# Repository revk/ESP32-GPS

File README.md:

# ESP32-GPS

Now at [Codeberg](https://codeberg.org/RevK/ESP32-GPS)

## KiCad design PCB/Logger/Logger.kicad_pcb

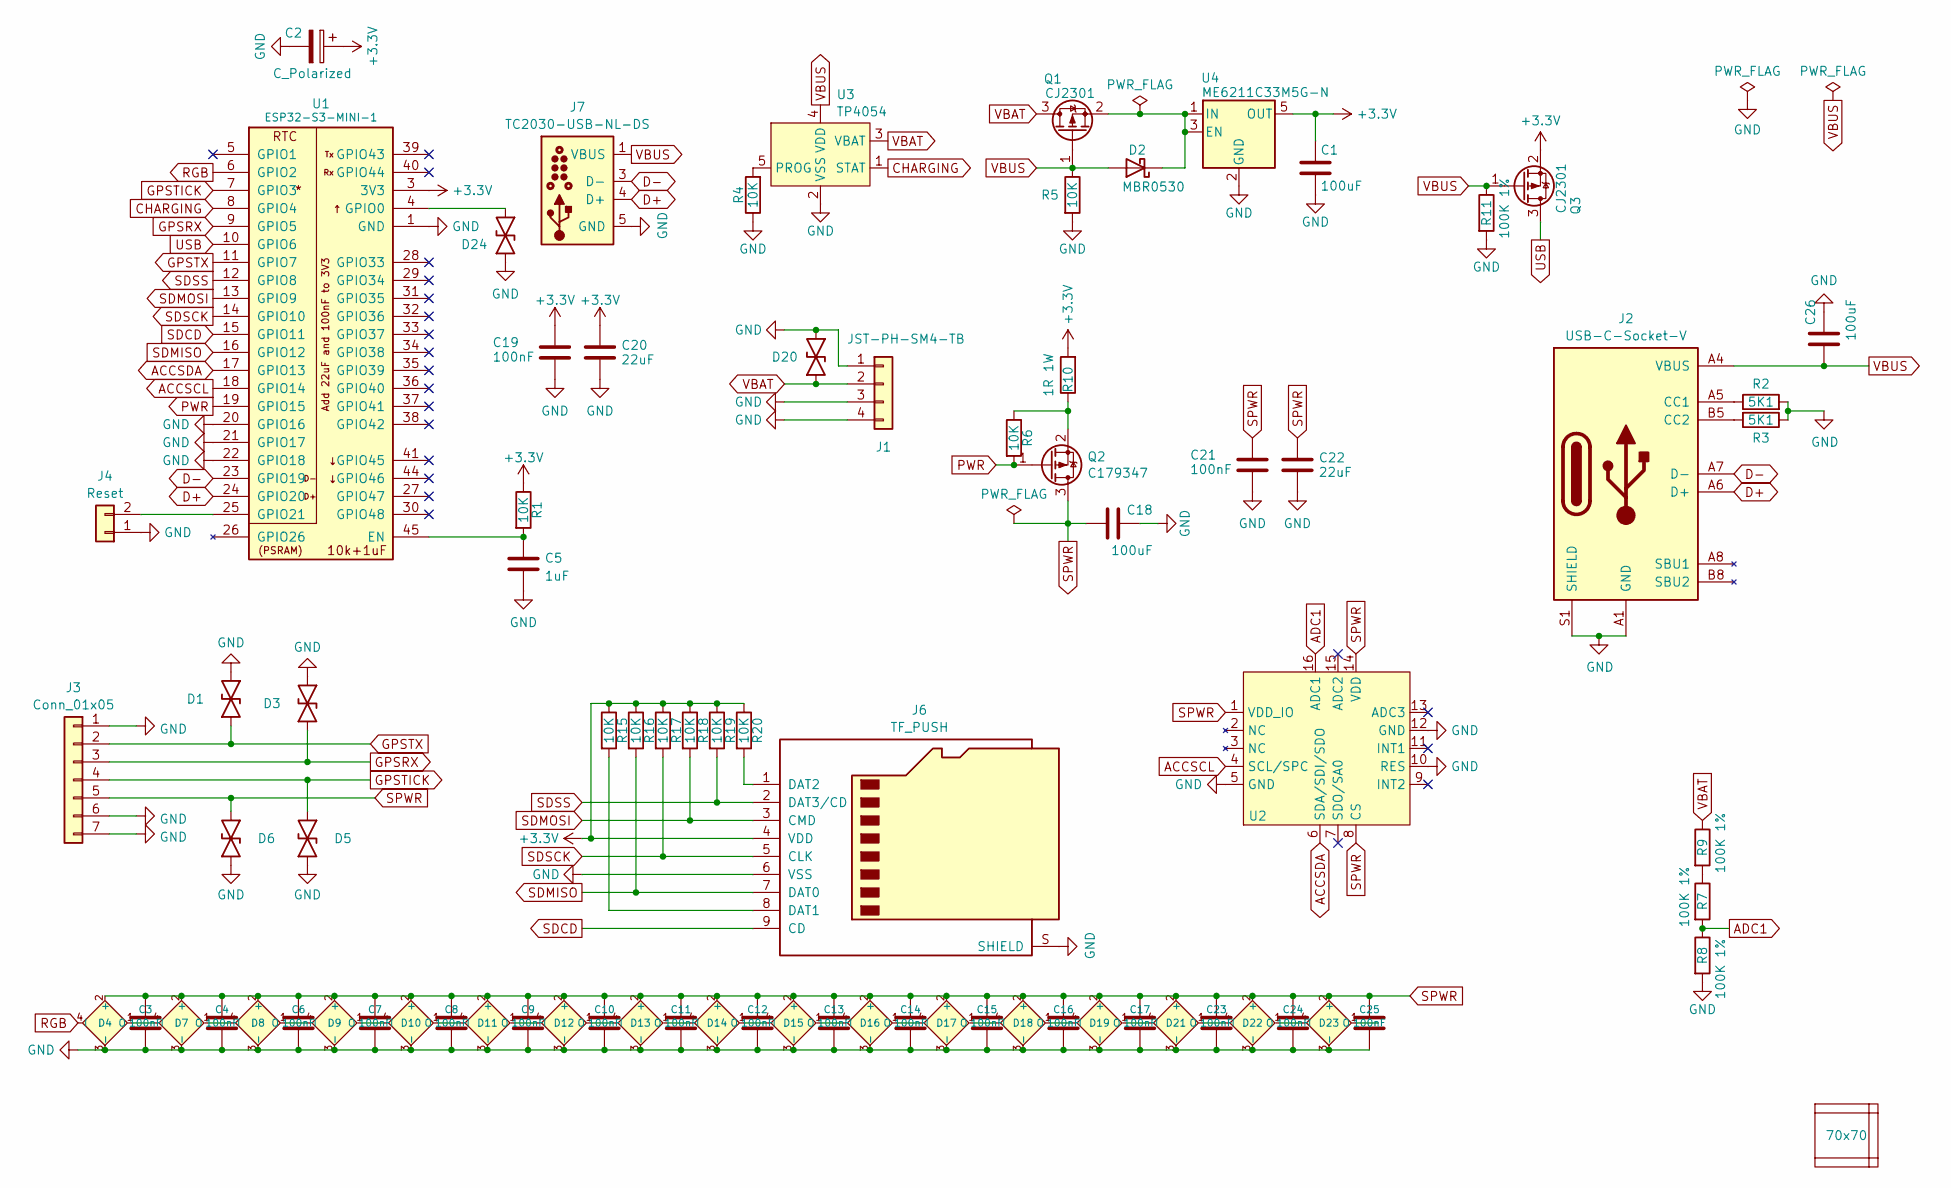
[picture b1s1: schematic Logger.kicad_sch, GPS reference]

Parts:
C1, C18, C26: 100uF; C_0805; MPN C141660
C2: C_Polarized; CP_EIA-7343-31_Kemet-D; MPN C106188
C3, C4, C6, C7, C8, C9, C10, C11, C12, C13, C14, C15, C16, C17, C19, C21, C23, C24, C25: 100nF; C_0402
C5: 1uF; C_0402
C20, C22: 22uF; C_0603
D1, D3, D5, D6, D20, D24: DFN1006-2L; MPN C5137770
D2: MBR0530; D_SOD-123; MPN C5204746
D4, D7, D8, D9, D10, D11, D12, D13, D14, D15, D16, D17, D18, D19, D21, D22, D23: XL-1010RGBC-WS2812B; SMD1010; MPN C5349953
J1: JST-PH-SM4-TB; JST_PH_S2B-PH-SM4-TB_1x02-1MP_P2.00mm_Horizontal; MPN C295747
J2: USB-C-Socket-V; USB-C-Socket-H; MPN C709357
J3: Conn_01x05; PTSM-HH-5-RA-SMD; Part Name PTSM 0,5/ 5-HH0-2,5-SMD WH R32
J4: Reset; AA-Pad
J6: TF_PUSH; MPN C393941
J7: TC2030-USB-NL-DS; Tag-Connect_TC2030-IDC-NL_2x03_P1.27mm_Vertical
PCB1: 70x70; PCB7070
Q1, Q3: CJ2301; SOT-23; MPN C5224170
Q2: C179347; SOT-23; MPN C3034
R1, R4, R5, R6, R15, R16, R17, R18, R19, R20: 10K; R_0402
R2, R3: 5K1; R_0402
R7, R8, R9, R11: 100K 1%; R_0402; MPN C5139597
R10: 1R 1W; R_1218; MPN C175540
U1: ESP32-S3-MINI-1; MPN C3013941
U2: LGA-16_3x3mm_P0.5mm_LayoutBorder3x5y; MPN C15134
U3: TP4054; SOT-23-5; MPN C668215
U4: ME6211C33M5G-N; SOT-23-5; MPN C82942
V1, V2, V4: VCUT70N

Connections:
+3.3V: C1.1, C2.1, C19.1, C20.1, J6.4 (VDD), Q3.2 (S), R1.1, R10.2, R15.1, R16.1, R17.1, R18.1, R19.1, R20.1, U1.3 (3V3), U4.5 (OUT)
ACCSCL: U1.18 (GPIO14), U2.4 (SCL/SPC)
ACCSDA: U1.17 (GPIO13), U2.6 (SDA/SDI/SDO)
ADC1: R7.2, R8.1, U2.16 (ADC1)
CHARGING: U1.8 (GPIO4), U3.1 (STAT)
D+: J2.A6 (D+), J2.B6 (D+), J7.4 (D+), U1.24 (GPIO20)
D-: J2.A7 (D-), J2.B7 (D-), J7.3 (D-), U1.23 (GPIO19)
GND: C1.2, C2.2, C3.2, C4.2, C5.2, C6.2, C7.2, C8.2, C9.2, C10.2, C11.2, C12.2, C13.2, C14.2, C15.2, C16.2, C17.2, C18.2, C19.2, C20.2, C21.2, C22.2, C23.2, C24.2, C25.2, C26.2, D1.1, D3.1, D4.3 (-), D5.1, D6.1, D7.3 (-), D8.3 (-), D9.3 (-), D10.3 (-), D11.3 (-), D12.3 (-), D13.3 (-), D14.3 (-), D15.3 (-), D16.3 (-), D17.3 (-), D18.3 (-), D19.3 (-), D20.1, D21.3 (-), D22.3 (-), D23.3 (-), D24.2, J1.1, J1.3, J1.4, J2.A1 (GND), J2.A12 (GND), J2.B1 (GND), J2.B12 (GND), J2.S1 (SHIELD), J3.1, J3.6, J3.7, J4.1, J6.6 (VSS), J6.S (SHIELD), J7.5 (GND), J7.6 (GND), R2.2, R3.1, R4.1, R5.2, R8.2, R11.2, U1.1 (GND), U1.2 (GND), U1.20 (GPIO16), U1.21 (GPIO17), U1.22 (GPIO18), U1.42 (GND), U1.43 (GND), U1.46 (GND), U1.47 (GND), U1.48 (GND), U1.49 (GND), U1.50 (GND), U1.51 (GND), U1.52 (GND), U1.53 (GND), U1.54 (GND), U1.55 (GND), U1.56 (GND), U1.57 (GND), U1.58 (GND), U1.59 (GND), U1.60 (GND), U1.61 (GND), U1.62 (GND), U1.63 (GND), U1.64 (GND), U1.65 (GND), U2.5 (GND), U2.10 (RES), U2.12 (GND), U3.2 (VSS), U4.2 (GND)
GPSRX: D3.2, J3.3, U1.9 (GPIO5)
GPSTICK: D5.2, J3.4, U1.7 (GPIO3)
GPSTX: D1.2, J3.2, U1.11 (GPIO7)
unnamed: D2.1 (K), Q1.2 (S), U4.1 (IN), U4.3 (EN)
unnamed: D4.1 (O), D7.4 (I)
unnamed: D7.1 (O), D8.4 (I)
unnamed: D8.1 (O), D9.4 (I)
unnamed: D9.1 (O), D10.4 (I)
unnamed: D10.1 (O), D11.4 (I)
unnamed: D11.1 (O), D12.4 (I)
unnamed: D12.1 (O), D13.4 (I)
unnamed: D13.1 (O), D14.4 (I)
unnamed: D14.1 (O), D15.4 (I)
unnamed: D15.1 (O), D16.4 (I)
unnamed: D16.1 (O), D17.4 (I)
unnamed: D17.1 (O), D18.4 (I)
unnamed: D18.1 (O), D19.4 (I)
unnamed: D19.1 (O), D21.4 (I)
unnamed: D21.1 (O), D22.4 (I)
unnamed: D22.1 (O), D23.4 (I)
unnamed: J2.A5 (CC1), R2.1
unnamed: J2.B5 (CC2), R3.2
unnamed: J4.2, U1.25 (GPIO21)
unnamed: J6.8 (DAT1), R15.2
unnamed: J6.1 (DAT2), R20.2
unnamed: Q2.2 (S), R6.1, R10.1
unnamed: R7.1, R9.2
unnamed: C5.1, R1.2, U1.45 (EN)
unnamed: D24.1, U1.4 (GPIO0)
unnamed: R4.2, U3.5 (PROG)
PWR: Q2.1 (G), R6.2, U1.19 (GPIO15)
RGB: D4.4 (I), U1.6 (GPIO2)
SDCD: J6.9 (CD), U1.15 (GPIO11)
SDMISO: J6.7 (DAT0), R16.2, U1.16 (GPIO12)
SDMOSI: J6.3 (CMD), R18.2, U1.13 (GPIO9)
SDSCK: J6.5 (CLK), R17.2, U1.14 (GPIO10)
SDSS: J6.2 (DAT3/CD), R19.2, U1.12 (GPIO8)
SPWR: C3.1, C4.1, C6.1, C7.1, C8.1, C9.1, C10.1, C11.1, C12.1, C13.1, C14.1, C15.1, C16.1, C17.1, C18.1, C21.1, C22.1, C23.1, C24.1, C25.1, D4.2 (+), D6.2, D7.2 (+), D8.2 (+), D9.2 (+), D10.2 (+), D11.2 (+), D12.2 (+), D13.2 (+), D14.2 (+), D15.2 (+), D16.2 (+), D17.2 (+), D18.2 (+), D19.2 (+), D21.2 (+), D22.2 (+), D23.2 (+), J3.5, Q2.3 (D), U2.1 (VDD_IO), U2.8 (CS), U2.14 (VDD)
USB: Q3.3 (D), U1.10 (GPIO6)
VBAT: D20.2, J1.2, Q1.3 (D), R9.1, U3.3 (VBAT)
VBUS: C26.1, D2.2 (A), J2.A4 (VBUS), J2.A9 (VBUS), J2.B4 (VBUS), J2.B9 (VBUS), J7.1 (VBUS), J7.2 (VBUS), Q1.1 (G), Q3.1 (G), R5.1, R11.1, U3.4 (VDD)

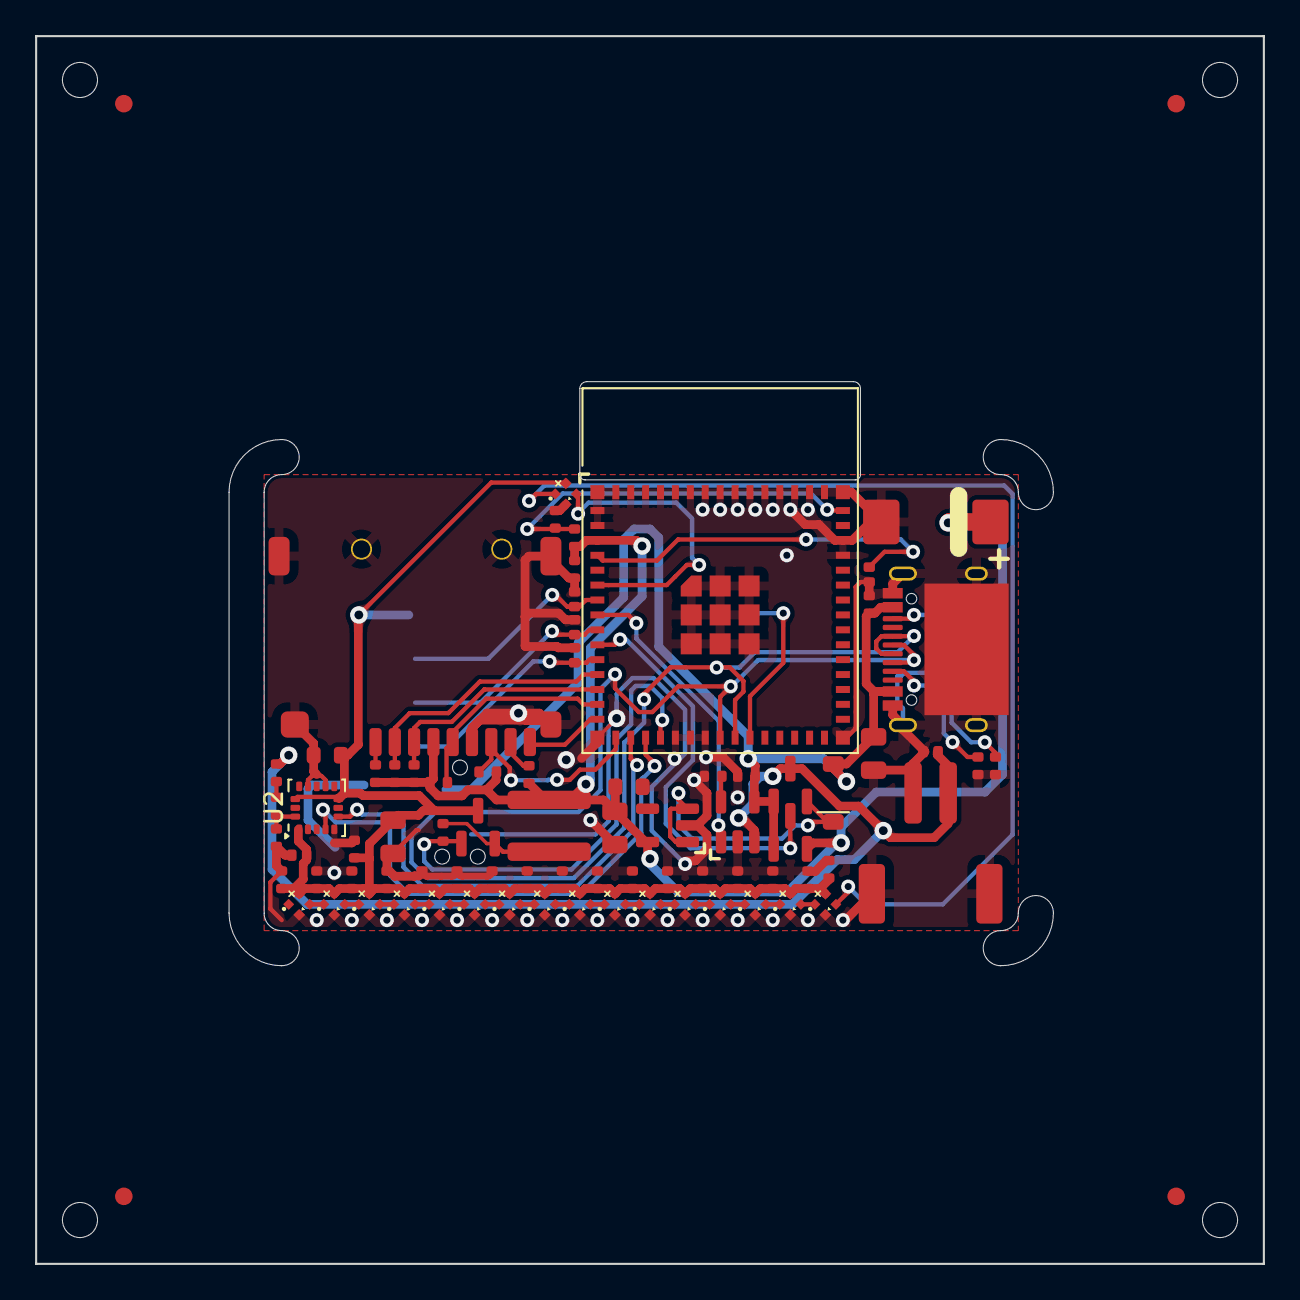
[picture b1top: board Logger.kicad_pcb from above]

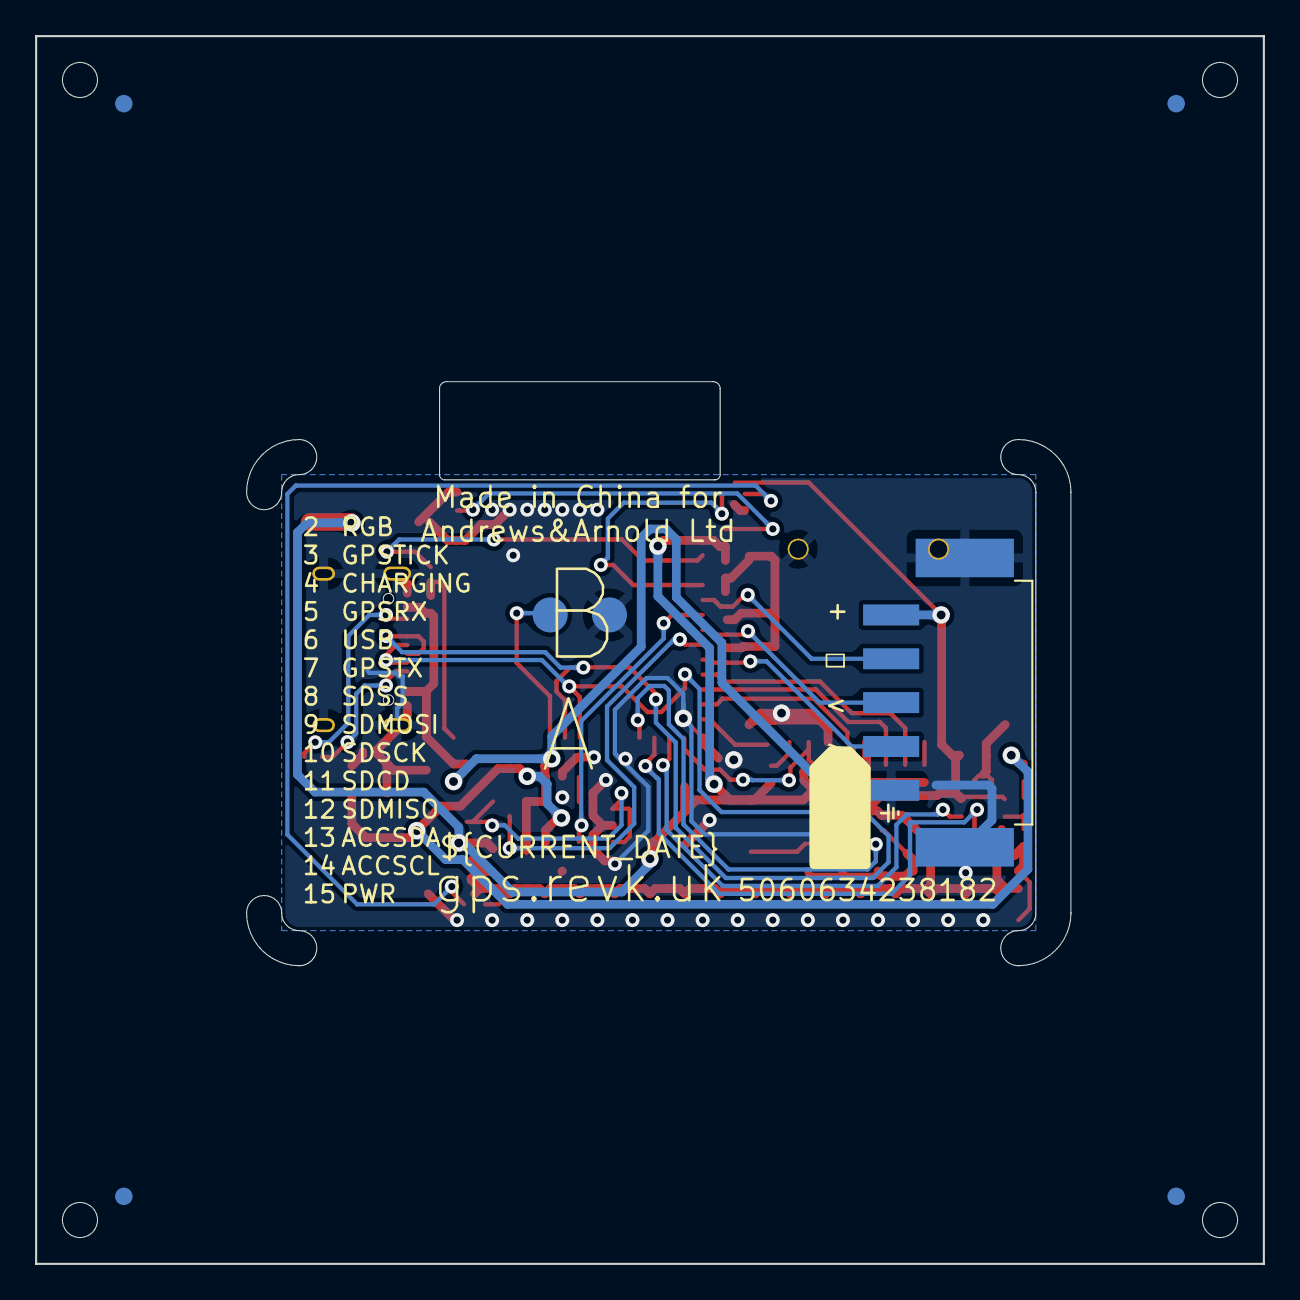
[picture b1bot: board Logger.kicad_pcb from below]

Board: 2 copper layers, 70.0 x 70.0 mm, 84 parts (4 on the bottom side), 49 nets.

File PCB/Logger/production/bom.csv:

Designator,Footprint,Quantity,Value,LCSC Part #
"C1, C18, C26",C_0805,3,100uF,C141660
"C10, C11, C12, C13, C14, C15, C16, C17, C19, C21, C23, C24, C25, C3, C4, C6, C7, C8, C9",C_0402,19,100nF,
C2,CP_EIA-7343-31_Kemet-D,1,C_Polarized,C106188
"C20, C22",C_0603,2,22uF,
C5,C_0402,1,1uF,
"D1, D20, D24, D3, D5, D6",DFN1006-2L,6,~,C5137770
"D10, D11, D12, D13, D14, D15, D16, D17, D18, D19, D21, D22, D23, D4, D7, D8, D9",SMD1010,17,XL-1010RGBC-WS2812B,C5349953
D2,D_SOD-123,1,MBR0530,
J1,JST_PH_S2B-PH-SM4-TB_1x02-1MP_P2.00mm_Horizontal,1,JST-PH-SM4-TB,C295747
J2,USB-C-Socket-H,1,USB-C-Socket-V,C709357
J4,AA-Pad,1,Reset,
J6,TF_PUSH,1,TF_PUSH,C393941
"Q1, Q3",SOT-23,2,CJ2301,C5224170
Q2,SOT-23,1,C179347,C3034
"R1, R15, R16, R17, R18, R19, R20, R4, R5, R6",R_0402,10,10K,
R10,R_1218,1,1R 1W,C175540
"R11, R7, R8, R9",R_0402,4,100K 1%,C5139597
"R2, R3",R_0402,2,5K1,
U1,ESP32-S3-MINI-1,1,ESP32-S3-MINI-1,C3013941
U2,LGA-16_3x3mm_P0.5mm_LayoutBorder3x5y,1,~,C15134
U3,SOT-23-5,1,TP4054,C668215
U4,SOT-23-5,1,ME6211C33M5G-N,C82942

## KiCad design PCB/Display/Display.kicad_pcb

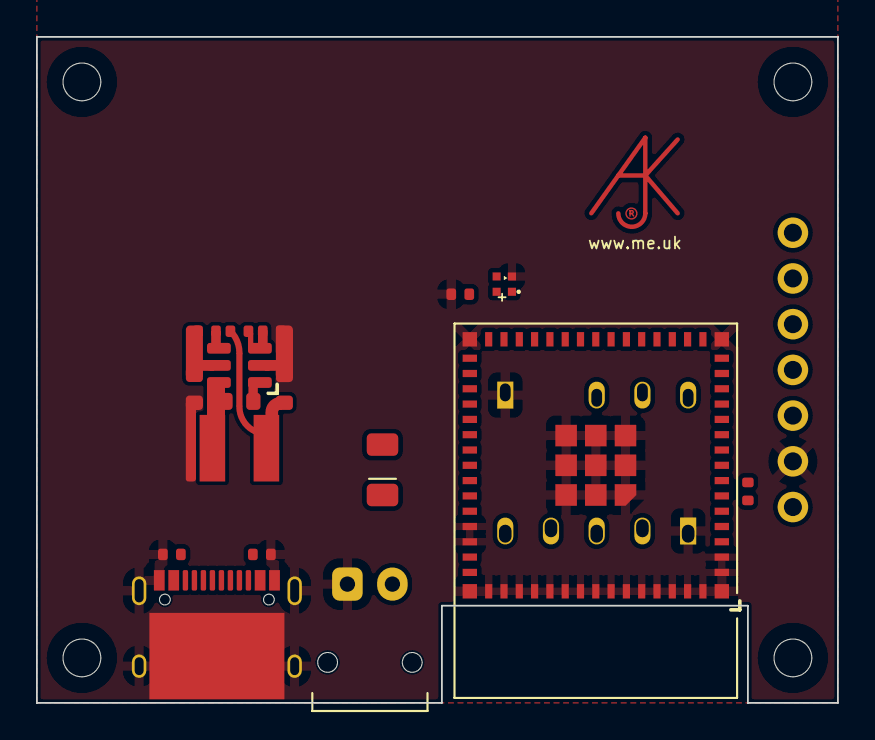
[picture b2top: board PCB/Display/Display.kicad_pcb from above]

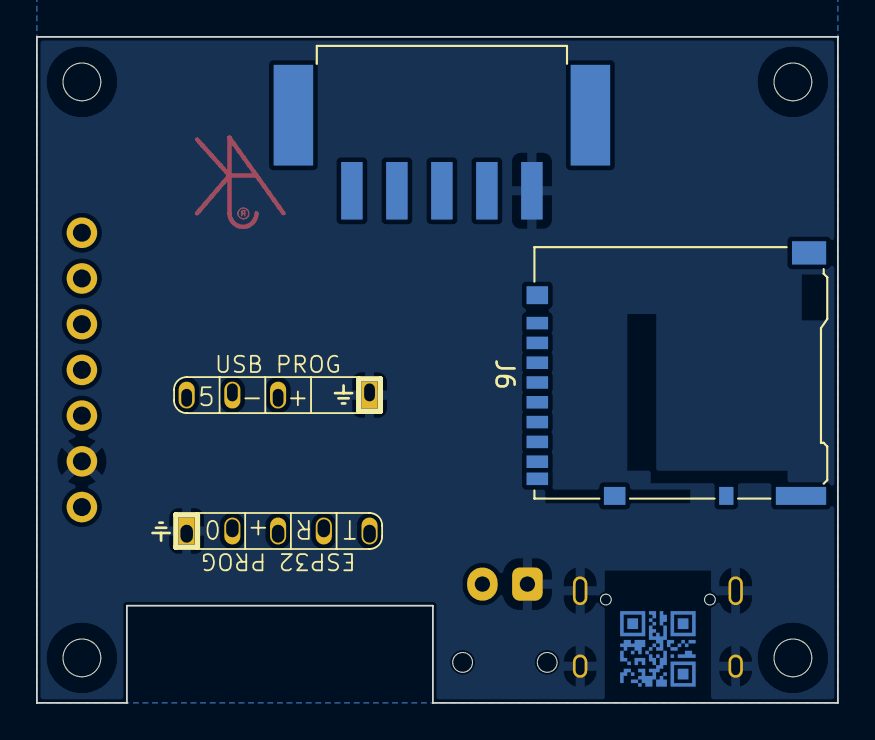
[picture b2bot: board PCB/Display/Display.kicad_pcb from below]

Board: 2 copper layers, 44.5 x 37.0 mm, 24 parts (5 on the bottom side), 21 nets, no tracks yet.

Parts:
C5: 1uF; C_0402
C6: 10uF 50V; C_0603_
C7: 10uF 6.3V; C_0603_
C8: 100nF; C_0603_
D1: D; D_1206
D4: XL-1010RGBC-WS2812B; SMD1010
J1: POWER; PTSM-HH1-2-RA
J2: USB-C-Socket-V; USB-C-Socket-H
J3: Conn_01x05; PTSM-HH-5-RA-SMD
J4: Shelly
J5: USB-PROG
J6: DM3AT-SF-PEJM5; microSD_HC_Hirose_DM3AT-SF-PEJM5
L2: 10uH; L_4x4_
Logo2: AJK
M1: OLED1.5-RGB
R1: 10K; R_0402
R2, R3: 5K1; R_0402
R13: 124k; R_0402_
R14: 40k2; R_0402_
R15: 1M; R_0402_
U1: ESP32-S3-MINI-1
U2: MD8942; SOT-23-6-MD8942
U5: QR; QR-SS

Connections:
+3V3: D4.2 (+), J3.5, J4.3 (3V3), M1.1 (Vcc), R1.1, U1.3 (3V3), U2.8 (VOUT)
D+: J2.A6 (D+), J2.B6 (D+), J5.3 (D+), U1.24 (GPIO20)
D-: J2.A7 (D-), J2.B7 (D-), J5.2 (D-), U1.23 (GPIO19)
DC: D1.1 (K), J1.2 (DC), U2.5 (VIN)
GND: C5.2, D4.3 (-), J1.1 (GND), J2.A1 (GND), J2.A12 (GND), J2.B1 (GND), J2.B12 (GND), J2.S1 (SHIELD), J3.1, J4.1 (GND), J5.4 (GND), M1.2 (GND), R2.2, R3.1, U1.1 (GND), U1.2 (GND), U1.42 (GND), U1.43 (GND), U1.46 (GND), U1.47 (GND), U1.48 (GND), U1.49 (GND), U1.50 (GND), U1.51 (GND), U1.52 (GND), U1.53 (GND), U1.54 (GND), U1.55 (GND), U1.56 (GND), U1.57 (GND), U1.58 (GND), U1.59 (GND), U1.60 (GND), U1.61 (GND), U1.62 (GND), U1.63 (GND), U1.64 (GND), U1.65 (GND), U2.2 (GND), U2.7 (GND)
GPSRX: J3.2, U1.36 (GPIO40)
GPSTICK: J3.4, U1.37 (GPIO41)
GPSTX: J3.3, U1.33 (GPIO37)
unnamed: J2.A5 (CC1), R2.1
unnamed: J2.B5 (CC2), R3.2
unnamed: J4.2 (0), U1.4 (GPIO0)
unnamed: J4.4 (Rx), U1.40 (GPIO44)
unnamed: J4.5 (Tx), U1.39 (GPIO43)
unnamed: C5.1, R1.2, U1.45 (EN)
OLED-CS: M1.5 (CS), U1.35 (GPIO39)
OLED-DC: M1.6 (DC), U1.19 (GPIO15)
OLED-MOSI: M1.3 (DIN), U1.16 (GPIO12)
OLED-RST: M1.7 (RST), U1.18 (GPIO14)
OLED-SCK: M1.4 (CLK), U1.34 (GPIO38)
RGB: D4.4 (I), U1.28 (GPIO33)
VBUS: D1.2 (A), J2.A4 (VBUS), J2.A9 (VBUS), J2.B4 (VBUS), J2.B9 (VBUS), J5.1 (VBUS)

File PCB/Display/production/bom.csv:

Designator,Footprint,Quantity,Value,LCSC Part #
C5,C_0402,1,1uF,
C6,C_0603_,1,10uF 50V,C1591
C7,C_0603_,1,10uF 6.3V,C1691
C8,C_0603_,1,100nF,
D1,D_1206,1,D,
D4,SMD1010,1,XL-1010RGBC-WS2812B,C5349953
J2,USB-C-Socket-H,1,USB-C-Socket-V,C709357
J3,PTSM-HH-5-RA-SMD,1,Conn_01x05,
J6,microSD_HC_Hirose_DM3AT-SF-PEJM5,1,DM3AT-SF-PEJM5,
L2,L_4x4_,1,10uH,
M1,OLED1.5-RGB,1,OLED1.5-RGB,
R1,R_0402,1,10K,
R13,R_0402_,1,124k,
R14,R_0402_,1,40k2,
R15,R_0402_,1,1M,
"R2, R3",R_0402,2,5K1,
U1,ESP32-S3-MINI-1,1,ESP32-S3-MINI-1,C3013941
U2,SOT-23-6-MD8942,1,MD8942,C2684786

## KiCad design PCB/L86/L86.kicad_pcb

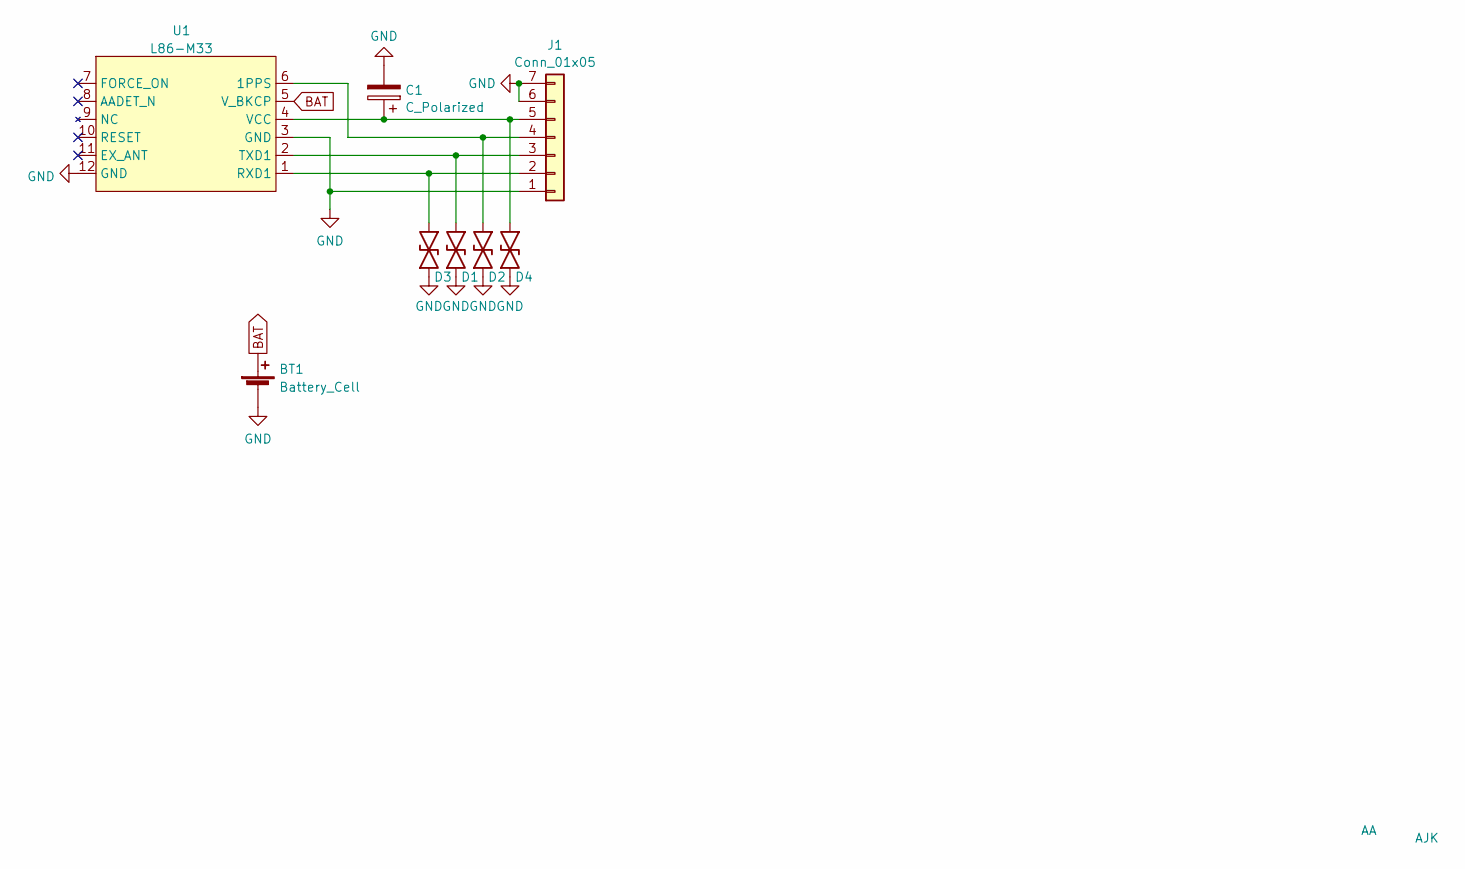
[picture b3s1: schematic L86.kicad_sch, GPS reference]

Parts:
BT1: Battery_Cell; Battery-Holder-2032
C1: C_Polarized; CP_EIA-7343-31_Kemet-D; MPN C106188
D1, D2, D3, D4: DFN1006-2L; MPN C5137770
J1: Conn_01x05; PTSM-HH-5-RA-P-SMD; Part name PTSM 0,5/ 5-HHI0-2,5SMDWH
Logo1: AA
Logo2: AJK
U1: L86-M33

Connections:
BAT: BT1.1 (+), U1.5 (V_BKCP)
GND: BT1.2 (-), C1.2, D1.2, D2.2, D3.2, D4.2, J1.1, J1.6, J1.7, U1.3 (GND), U1.12 (GND)
unnamed: D3.1, J1.2, U1.1 (RXD1)
unnamed: D1.1, J1.3, U1.2 (TXD1)
unnamed: D2.1, J1.4, U1.6 (1PPS)
unnamed: C1.1, D4.1, J1.5, U1.4 (VCC)

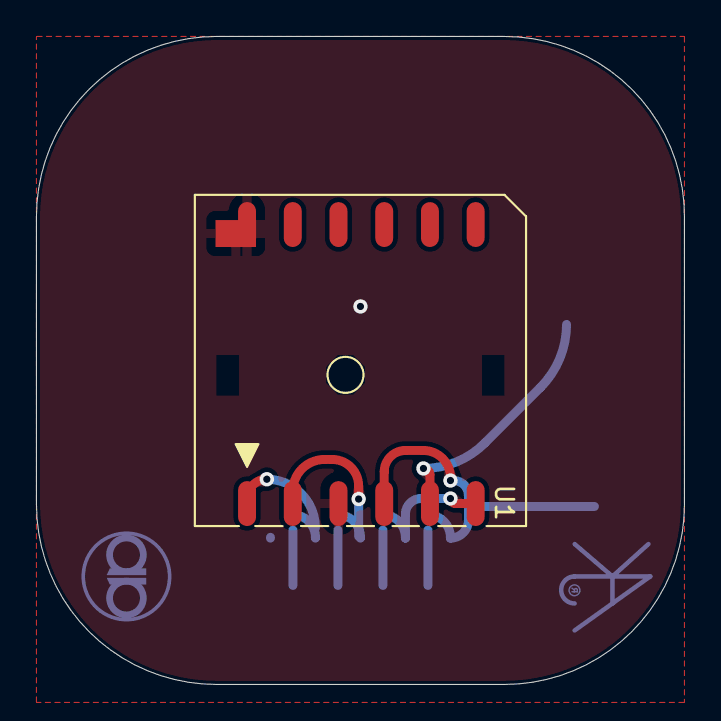
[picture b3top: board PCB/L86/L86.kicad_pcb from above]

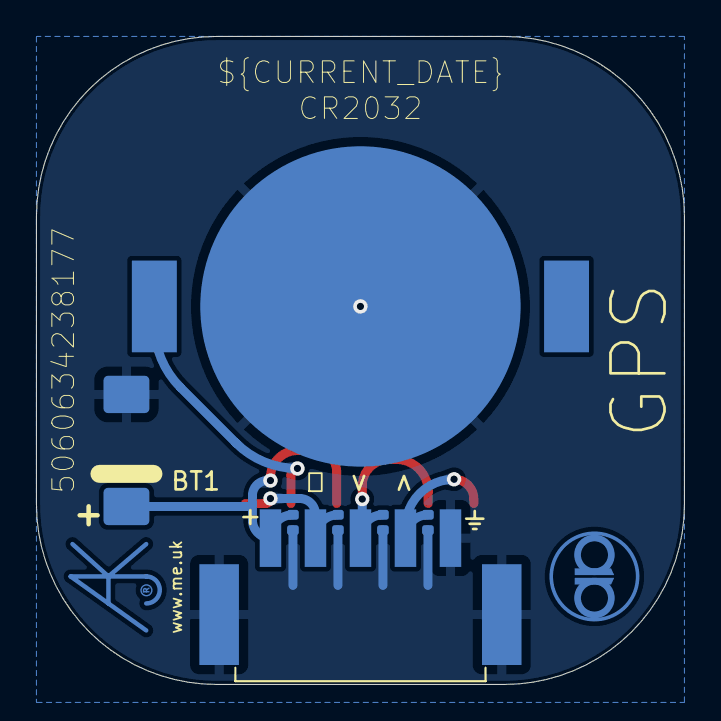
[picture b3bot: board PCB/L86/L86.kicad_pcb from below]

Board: 2 copper layers, 36.0 x 36.0 mm, 10 parts (9 on the bottom side), 6 nets.

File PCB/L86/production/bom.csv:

Designator,Footprint,Quantity,Value,LCSC Part #
BT1,Battery-Holder-2032,1,Battery_Cell,
C1,CP_EIA-7343-31_Kemet-D,1,C_Polarized,C106188
"D1, D2, D3, D4",DFN1006-2L,4,~,C5137770
J1,PTSM-HH-5-RA-P-SMD,1,Conn_01x05,
U1,L86-M33,1,L86-M33,

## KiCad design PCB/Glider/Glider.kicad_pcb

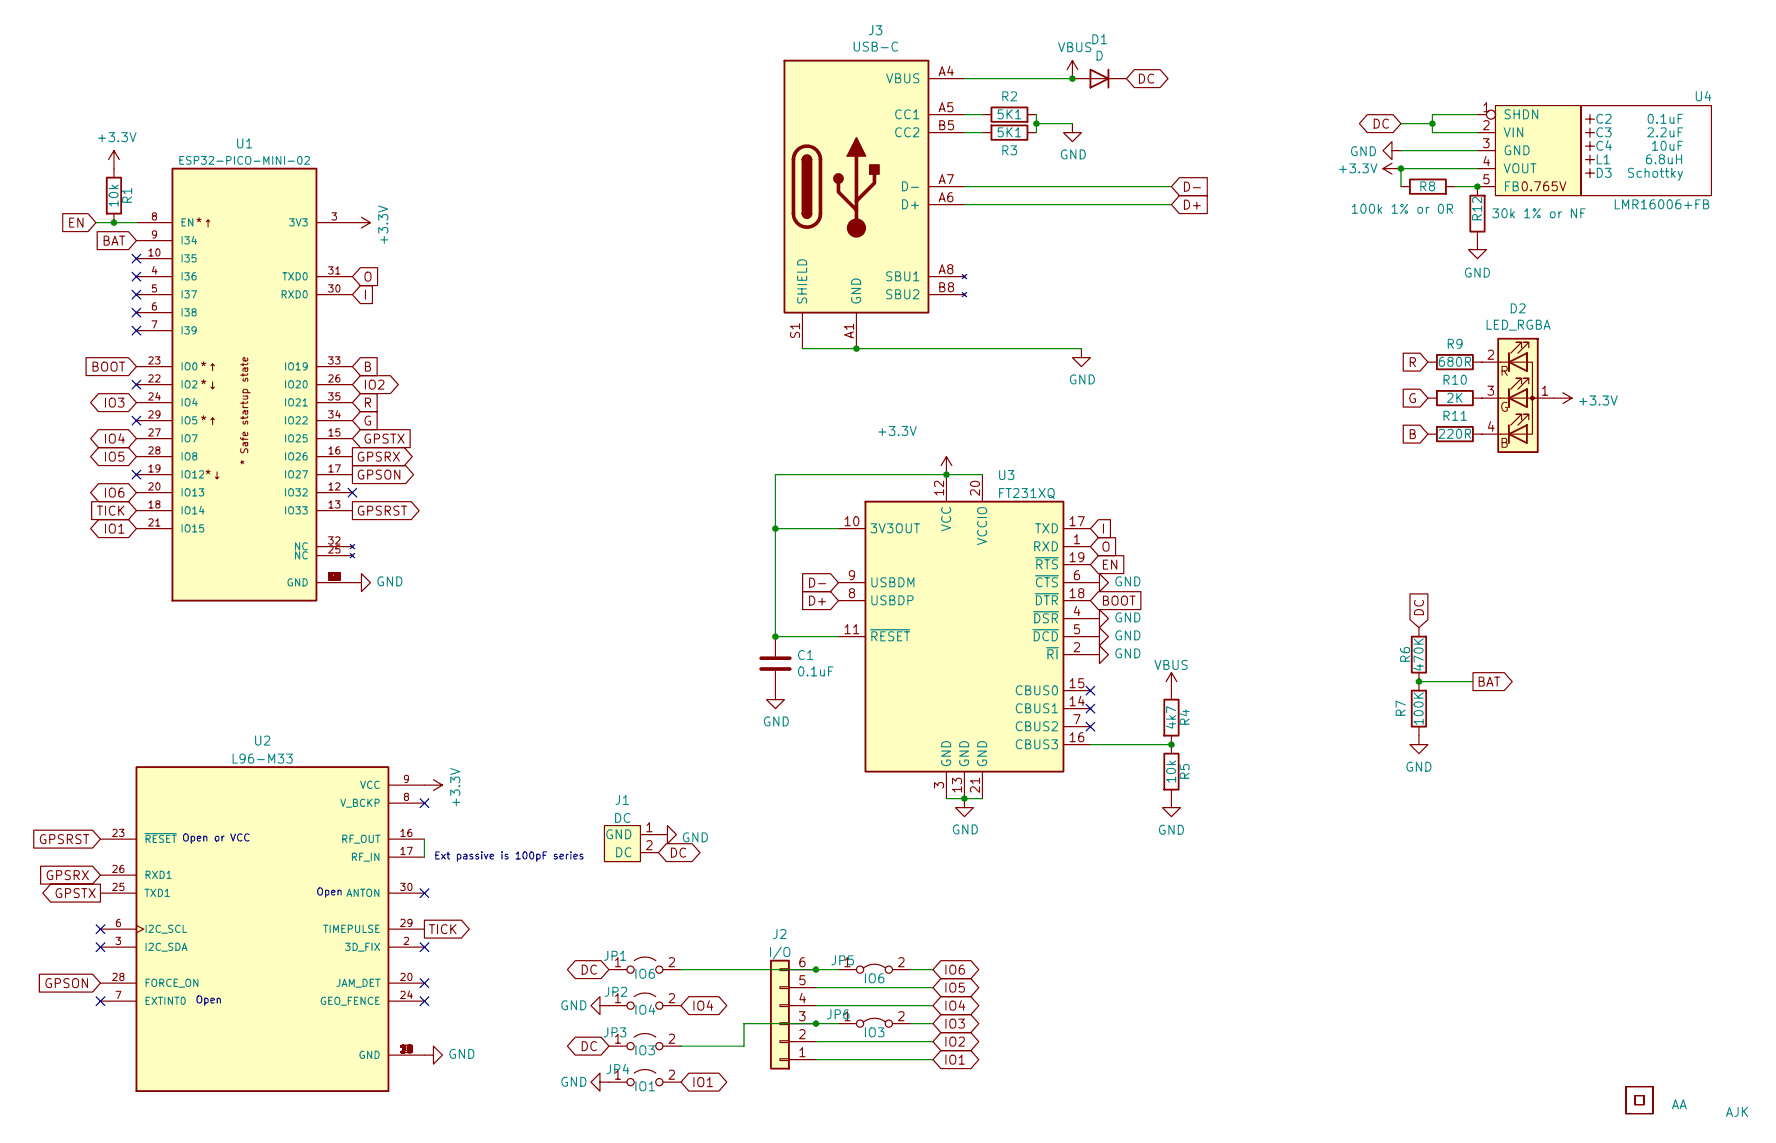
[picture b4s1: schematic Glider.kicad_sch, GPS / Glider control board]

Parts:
C1: 0.1uF; C_0603
C2: 0.1uF; Hidden
C3: 2.2uF; Hidden
C4: 10uF; Hidden
D1: D; D_1206_3216Metric
D2: LED_RGBA; LED-RGB-1.6x1.6
D3: Schottky; Hidden; Part No CD1206-B2100
J1: DC; Molex_MiniSPOX_H2RA
J2: I/O; Molex_MiniSPOX_H6RA
J3: USB-C; USC16-TR-Round
JP1: IO6; Pad_1206_0805_Open
JP2: IO4; Pad_1206_0805_Open
JP3: IO3; Pad_1206_0805_Open
JP4: IO1; Pad_1206_0805_Open
JP5: IO6; Pad_1206_0805_Bridged
JP6: IO3; Pad_1206_0805_Bridged
L1: 6.8uH; Hidden; Part No TYA4020
Logo1: AA
Logo2: AJK
R1, R5: 10k; R_0603
R2, R3: 5K1; R_0603
R4: 4k7; R_0603
R6: 470K; R_0603
R7: 100K; R_0603
R8: 100k 1% or 0R; R_0603
R9: 680R; R_0603
R10: 2K; R_0603
R11: 220R; R_0603
R12: 30k 1% or NF; R_0603
U1: ESP32-PICO-MINI-02; PARTREV v1.0
U2: L96-M33
U3: FT231XQ; QFN-20-1EP_4x4mm_P0.5mm_EP2.5x2.5mm
U4: LMR16006+FB; RegulatorBlockFB; Part No LMR16006YQ3
U5: QR; QR-SS

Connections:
+3V3: C1.1, D2.1 (A), R1.1, R8.1, U1.3 (3V3), U2.9 (VCC), U3.10 (3V3OUT), U3.11 (~RESET), U3.12 (VCC), U3.20 (VCCIO), U4.4 (VOUT)
B: R11.2, U1.33 (IO19)
BAT: R6.1, R7.2, U1.9 (I34)
BOOT: U1.23 (IO0), U3.18 (~DTR)
D+: J3.A6 (D+), J3.B6 (D+), U3.8 (USBDP)
D-: J3.A7 (D-), J3.B7 (D-), U3.9 (USBDM)
DC: D1.1 (K), J1.2 (DC), JP1.1 (A), JP3.1 (A), R6.2, U4.1 (SHDN), U4.2 (VIN)
EN: R1.2, U1.8 (EN), U3.19 (~RTS)
G: R10.2, U1.34 (IO22)
GND: C1.2, J1.1 (GND), J3.A1 (GND), J3.A12 (GND), J3.B1 (GND), J3.B12 (GND), J3.S1 (SHIELD), JP2.1 (A), JP4.1 (A), R2.2, R3.1, R5.2, R7.1, R12.1, U1.1 (GND), U1.2 (GND), U1.11 (GND), U1.14 (GND), U1.36 (GND), U1.37 (GND), U1.38 (GND), U1.39 (GND), U1.40 (GND), U1.41 (GND), U1.42 (GND), U1.43 (GND), U1.44 (GND), U1.45 (GND), U1.46 (GND), U1.47 (GND), U1.48 (GND), U1.49 (GND), U1.50 (GND), U1.51 (GND), U1.52 (GND), U1.53 (GND), U2.4 (GND), U2.5 (GND), U2.10 (GND), U2.11 (GND), U2.12 (GND), U2.13 (GND), U2.14 (GND), U2.15 (GND), U2.18 (GND), U2.19 (GND), U2.21 (GND), U2.22 (GND), U2.27 (GND), U2.31 (GND), U3.2 (~RI), U3.3 (GND), U3.4 (~DSR), U3.5 (~DCD), U3.6 (~CTS), U3.13 (GND), U3.21 (GND), U4.3 (GND)
GPSON: U1.17 (IO27), U2.28 (FORCE_ON)
GPSRST: U1.13 (IO33), U2.23 (~RESET)
GPSRX: U1.16 (IO26), U2.26 (RXD1)
GPSTX: U1.15 (IO25), U2.25 (TXD1)
I: U1.30 (RXD0), U3.17 (TXD)
IO1: J2.1, JP4.2 (B), U1.21 (IO15)
IO2: J2.2, U1.26 (IO20)
IO3: JP6.2 (B), U1.24 (IO4)
IO4: J2.4, JP2.2 (B), U1.27 (IO7)
IO5: J2.5, U1.28 (IO8)
IO6: JP5.2 (B), U1.20 (IO13)
unnamed: D2.2 (RK), R9.1
unnamed: D2.3 (GK), R10.1
unnamed: D2.4 (BK), R11.1
unnamed: J2.3, JP3.2 (B), JP6.1 (A)
unnamed: J2.6, JP1.2 (B), JP5.1 (A)
unnamed: J3.A5 (CC1), R2.1
unnamed: J3.B5 (CC2), R3.2
unnamed: R4.2, R5.1, U3.16 (CBUS3)
unnamed: R8.2, R12.2, U4.5 (FB)
unnamed: U2.16 (RF_OUT), U2.17 (RF_IN)
O: U1.31 (TXD0), U3.1 (RXD)
R: R9.2, U1.35 (IO21)
TICK: U1.18 (IO14), U2.29 (TIMEPULSE)
VBUS: D1.2 (A), J3.A4 (VBUS), J3.A9 (VBUS), J3.B4 (VBUS), J3.B9 (VBUS), R4.1

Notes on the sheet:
Open
Ext passive is 100pF series
Open or VCC

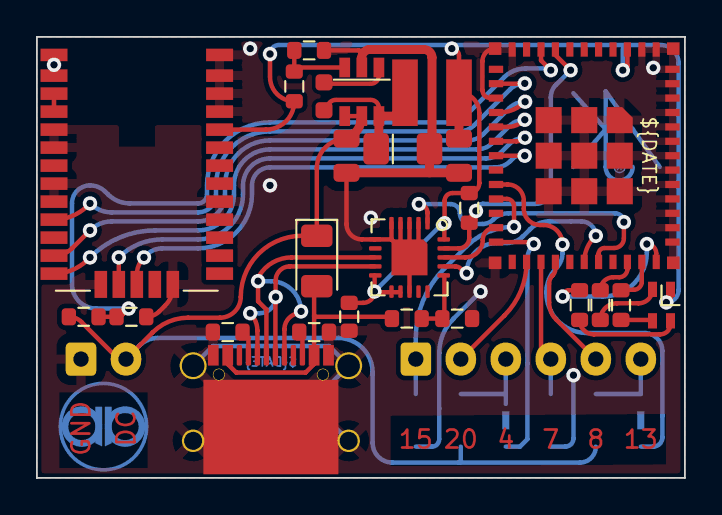
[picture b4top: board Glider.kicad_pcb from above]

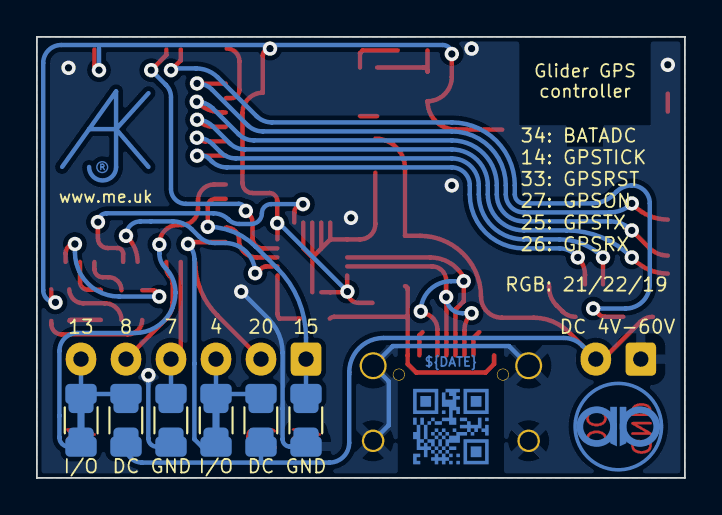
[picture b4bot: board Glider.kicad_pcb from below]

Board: 2 copper layers, 36.0 x 24.5 mm, 36 parts (9 on the bottom side), 35 nets.

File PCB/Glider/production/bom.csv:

Designator,Footprint,Quantity,Value,LCSC Part #
C1,C_0603,1,0.1uF,
C2,Hidden,1,0.1uF,
C3,Hidden,1,2.2uF,
C4,Hidden,1,10uF,
D1,1206,1,D,
D2,LED-RGB-1.6x1.6,1,LED_RGBA,
D3,Hidden,1,Schottky,
J1,Molex_MiniSPOX_H2RA,1,DC,
J2,Molex_MiniSPOX_H6RA,1,I/O,
J3,USC16-TR-Round,1,USB-C,
L1,Hidden,1,6.8uH,
"R1, R5",R_0603,2,10k,
R10,R_0603,1,2K,
R11,R_0603,1,220R,
R12,R_0603,1,30k 1% or NF,
"R2, R3",R_0603,2,5K1,
R4,R_0603,1,4k7,
R6,R_0603,1,470K,
R7,R_0603,1,100K,
R8,R_0603,1,100k 1% or 0R,
R9,R_0603,1,680R,
U1,ESP32-PICO-MINI-02,1,ESP32-PICO-MINI-02,
U2,L96-M33,1,L96-M33,
U3,QFN-20-1EP_4x4mm_P0.5mm_EP2.5x2.5mm,1,FT231XQ,
U4,RegulatorBlockFB,1,LMR16006+FB,

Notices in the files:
main/GPS.c:
Copyright (c) 2019-2024 Adrian Kennard, Andrews & Arnold Limited, see LICENSE file (GPL)
